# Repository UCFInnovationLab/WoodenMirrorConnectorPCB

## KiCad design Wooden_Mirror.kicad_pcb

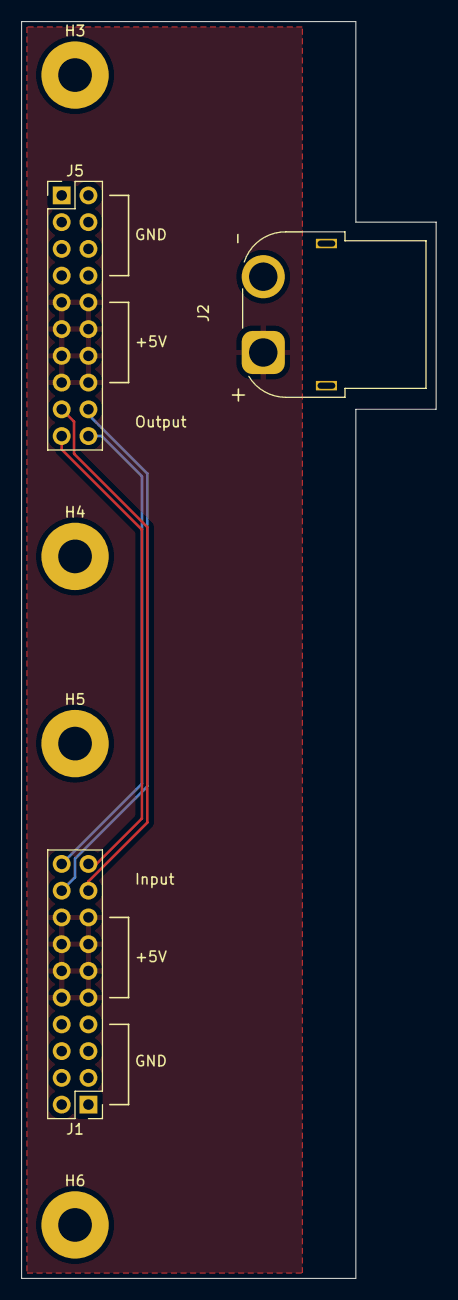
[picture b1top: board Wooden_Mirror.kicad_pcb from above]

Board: 2 copper layers, 39.4 x 119.4 mm, 7 parts (0 on the bottom side), 6 nets.

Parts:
H3, H4, H5, H6: MH; MountingHole_3.2mm_M3_Pad
J1, J5: Conn_02x10_Odd_Even; PinHeader_2x10_P2.54mm_Vertical
J2: Conn_01x02_Pin; AMASS_XT60PW-F_1x02_P7.20mm_Horizontal

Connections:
+5V: J1.9, J1.10, J1.11, J1.12, J1.13, J1.14, J1.15, J1.16, J2.1, J5.9, J5.10, J5.11, J5.12, J5.13, J5.14, J5.15, J5.16
/LED_DIN: J1.20, J5.20
/Serial_IN: J1.18, J5.18
GND: H3.1, H4.1, H5.1, H6.1, J1.1, J1.2, J1.3, J1.4, J1.5, J1.6, J1.7, J1.8, J2.2, J5.1, J5.2, J5.3, J5.4, J5.5, J5.6, J5.7, J5.8
unnamed: J1.17, J5.17
unnamed: J1.19, J5.19

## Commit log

2024-10-15 First Commit. 1st board sent
2024-10-15 2nd try
2024-10-25 done
2024-10-25 actually done can be sent to print
2024-10-25 nkmlkl
2024-10-25 now it can be sent
2024-10-25 mnm,
2024-10-25 jiok
2024-10-25 ALSO ready to be sent
2024-10-27 sent to jclpcb
2024-10-29 check connector
2024-10-29 cxeg
2024-10-29 bfgdfs
2024-10-29 v cbvx
2024-10-29 check this
2024-10-30 8;l7k865i7ju4635yq3r
2024-10-30 ;ouilykutryjethrgefa
2024-10-30 yrhterwq
2024-10-30 jhkjlk
2024-11-05 bfgdfsda
2024-11-05 final
